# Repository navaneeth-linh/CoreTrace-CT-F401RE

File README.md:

# CT-F401RE Evaluation Board
**Team:** CoreTrace  
**Designer:** S Navaneeth Krishna  
**Institution:** Muthoot Institute of Technology and Science (MITS), Kerala  
**Competition:** Mixed Traces PCB Design Competition — MEC 2026  

---

## Overview
CT-F401RE is a compact STM32F401RET6 evaluation and development board 
designed for the Mixed Traces PCB Design Competition organized by 
Mixed Signals, the Electronics Association of MEC. The board is 
inspired by the STM32 NUCLEO-F401RE reference design and provides 
essential facilities for programming, debugging, and general-purpose 
embedded development.

---

## Features
- STM32F401RET6 LQFP-64 microcontroller
- USB Micro-B interface for power and communication
- SWD debug and programming header (6-pin)
- UART communication header (4-pin)
- SPI communication header (6-pin)
- I2C communication header (4-pin)
- 18 GPIO pins exposed via CN1 and CN2 headers
- 8MHz HSE crystal oscillator
- AMS1117-3.3 LDO voltage regulator (5V → 3.3V)
- 4 LED indicators (PWR / USR / TX / RX)
- Reset tactile button
- User tactile button
- BOOT0 SPDT slide switch
- 100 × 100mm 2-layer PCB
- Designed in KiCad 10.0.5

---

## Design Decisions

### Power Supply
- AMS1117-3.3 LDO chosen for simplicity, availability and low cost
- USB Micro-B as power input via VBUS (5V)
- Bulk capacitors (22µF) on both input and output of regulator
- 100nF ceramic decoupling caps on all MCU VDD pins
- Ferrite bead (120R) on VDDA/VREF+ supply for analog noise filtering
- VCAP1 = 2.2µF for STM32F401RE internal voltage regulator stability

### USB
- 22Ω series resistors on D+ and D− for signal integrity
- Internal 1.5kΩ pullup on D+ for USB Full Speed detection
- USB Micro-B connector on board edge for easy access

### Clock
- 8MHz HSE crystal with 20pF load capacitors
- Crystal placed close to PH0/PH1 pins for short traces

### BOOT0
- SPDT slide switch for easy BOOT0 selection
- FLASH position → normal boot from flash
- BOOT position → bootloader mode
- 10kΩ pulldown resistor as default LOW state

### GPIO
- CN1 exposes: 3.3V, PA0, PA1, PA8, PA9, PA10, PA15, PB1, PB2, GND
- CN2 exposes: 3.3V, PB3, PB4, PB5, PB6, PB7, PB10, PB12, PB13, GND
- All unused PC pins assigned no-connect flags

### PCB
- SMD components throughout for compact layout
- 0402 package for resistors and small capacitors
- 0805 package for LEDs and bulk capacitors
- GND copper pour on both layers
- Track widths: 0.2mm signal, 0.3mm MCU power, 0.5mm 3.3V, 0.8mm VBUS

---

## Design Status

| Task | Status |
|---|---|
| Schematic | ✅ Complete |
| ERC | ✅ Clean (0 errors, 0 warnings) |
| PCB Layout | ✅ Complete |
| Routing | ✅ Complete |
| DRC | ✅ Clean (0 errors, 1 warning) |
| Silkscreen | ✅ Complete |
| BOM | ✅ Complete |
| Documentation | ✅ Complete |

---

## Known Issues and Warnings

### DRC Warning — Footprint Mismatch
**Warning:**    

**Component:** SW1 — BOOT0 SPDT Switch

**Reason:** The SPDT switch footprint was 
modified to fix a silkscreen overlap with 
the board edge cut. The silkscreen of the 
original footprint extended beyond the PCB 
boundary causing a DRC violation. The 
footprint silkscreen was moved inward 
resulting in a minor library mismatch warning.

**Impact:** None — footprint is electrically 
correct and physically accurate. This is a 
cosmetic library mismatch only.

**DRC Summary:**
| Type | Count |
|---|---|
| Errors | 0 ✅ |
| Warnings | 1 ⚠️ |
| Unconnected nets | 0 ✅ |

---

## Screenshots

### Block Diagram 

### Schematic

### PCB Layout

### PCB 3D View

### PCB 3D View

### ERC Results

### DRC Results

---

## Bill of Materials (BOM) with Estimated Cost

| Ref | Component | Value | Package | Qty | Unit Price (₹) | Total (₹) |
|---|---|---|---|---|---|---|
| U1 | STM32F401RET6 | MCU | LQFP-64 | 1 | ₹450 | ₹450 |
| U2 | AMS1117-3.3 | LDO Regulator | SOT-223 | 1 | ₹15 | ₹15 |
| Y1 | Crystal | 8MHz | SMD 3225 | 1 | ₹25 | ₹25 |
| C1, C2 | Capacitor | 22µF | 0805 | 2 | ₹5 | ₹10 |
| C13 | Capacitor | 2.2µF | 0805 | 1 | ₹4 | ₹4 |
| C14, C15 | Capacitor | 1µF | 0805 | 2 | ₹3 | ₹6 |
| C6,C7,C8,C9,C10,C11 | Capacitor | 100nF | 0402 | 6 | ₹2 | ₹12 |
| C3, C12 | Capacitor | 10nF | 0402 | 2 | ₹2 | ₹4 |
| C4, C5 | Capacitor | 20pF | 0402 | 2 | ₹2 | ₹4 |
| R2, R6 | Resistor | 10kΩ | 0402 | 2 | ₹1 | ₹2 |
| R3, R4 | Resistor | 4.7kΩ | 0402 | 2 | ₹1 | ₹2 |
| R1 | Resistor | 1kΩ | 0402 | 1 | ₹1 | ₹1 |
| R5, R7, R8 | Resistor | 330Ω | 0402 | 3 | ₹1 | ₹3 |
| R9, R10 | Resistor | 22Ω | 0402 | 2 | ₹1 | ₹2 |
| R_USB | Resistor | 1.5kΩ | 0402 | 1 | ₹1 | ₹1 |
| FB1 | Ferrite Bead | 120R | 0805 | 1 | ₹8 | ₹8 |
| D1 | LED | Red | 0805 | 1 | ₹5 | ₹5 |
| D2 | LED | Green | 0805 | 1 | ₹5 | ₹5 |
| D3 | LED | Blue | 0805 | 1 | ₹5 | ₹5 |
| D4 | LED | Yellow | 0805 | 1 | ₹5 | ₹5 |
| SW2 | Tactile Switch | Reset | SMD 6×6mm | 1 | ₹8 | ₹8 |
| SW3 | Tactile Switch | User | SMD 6×6mm | 1 | ₹8 | ₹8 |
| SW1 | SPDT Switch | BOOT0 | SMD | 1 | ₹12 | ₹12 |
| J1 | USB Micro-B | Connector | SMD | 1 | ₹20 | ₹20 |
| CN1, CN2 | Pin Header | 2.54mm 1×10 | THT | 2 | ₹8 | ₹16 |
| J5 | Pin Header | 2.54mm 1×06 | THT | 1 | ₹5 | ₹5 |
| J2, J3 | Pin Header | 2.54mm 1×04 | THT | 2 | ₹4 | ₹8 |
| J4 | Pin Header | 2.54mm 1×06 | THT | 1 | ₹5 | ₹5 |
| — | PCB Manufacturing | 2-layer 100×100mm | — | 1 | ₹150 | ₹150 |
| **Total** | | | | | | **₹811** |

> **Note:** Prices are approximate Indian market rates
> sourced from Robu.in, Evelta, and ElectronicsComp.
> Actual prices may vary by supplier and quantity.
> PCB cost based on single unit prototype pricing.

## Tools Used
- KiCad 10.0.5
- STM32F401RET6 Datasheet
- NUCLEO-F401RE Reference Schematic (MB1136)
- STM32F401RE Reference Manual

---

## Competition Details
**Competition:** Mixed Traces PCB Design Competition  
**Organizer:** Mixed Signals — Electronics Association of MEC  
**Reference:** STM32 NUCLEO-F401RE (MB1136)  
**Submission Date:** September 2026  

---

*© 2026 CoreTrace — S Navaneeth Krishna — MITS Kerala*

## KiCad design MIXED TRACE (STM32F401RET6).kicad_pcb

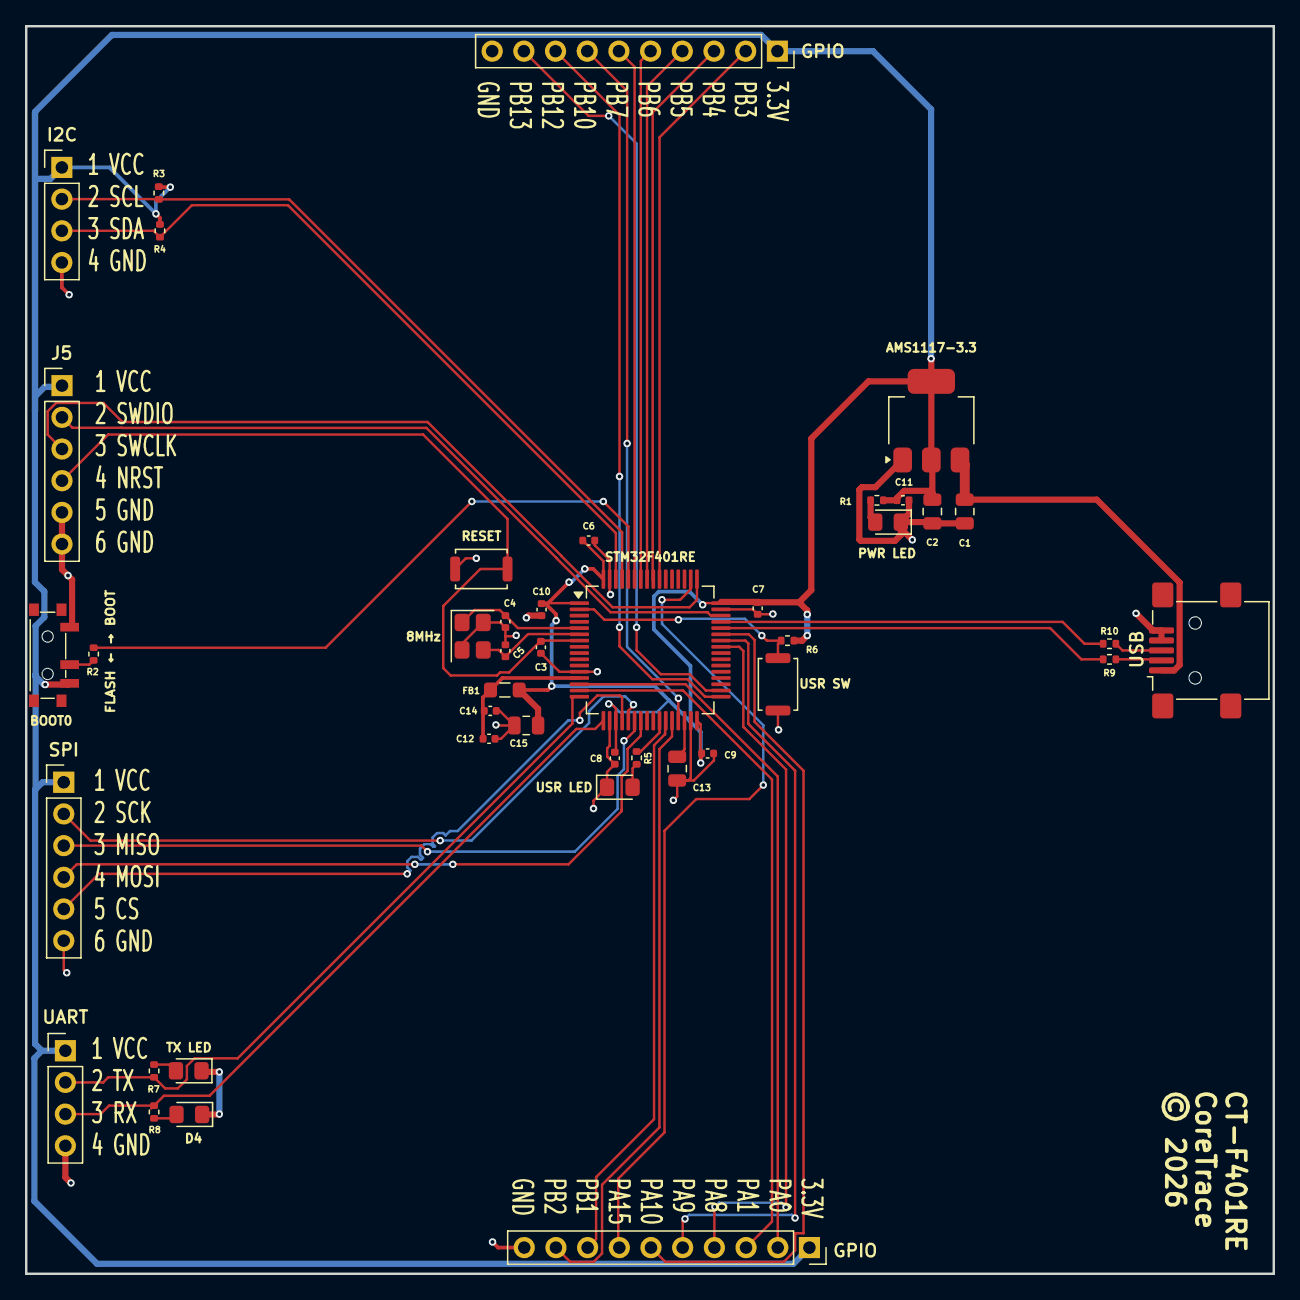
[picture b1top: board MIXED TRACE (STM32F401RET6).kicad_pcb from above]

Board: 2 copper layers, 100.0 x 100.0 mm, 43 parts (0 on the bottom side), 46 nets.

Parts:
8MHz: 8MHz; Crystal_SMD_3225-4Pin_3.2x2.5mm
AMS1117-3.3: AMS1117-3.3; SOT-223-3_TabPin2
BOOT0: BOOT_SW; SW_SPDT_PCM12
C1, C2: 22uF; C_0805_2012Metric
C3, C6, C7, C8, C9, C10, C11: 100nF; C_0402_1005Metric
C4, C5: 20pF; C_0402_1005Metric
C12, C14: 10nF; C_0402_1005Metric
C13: 2.2uF; C_0805_2012Metric
C15: 1uF; C_0805_2012Metric
D4: YELLOW; LED_0805_2012Metric_Pad1.15x1.40mm_HandSolder
FB1: 120R; L_0805_2012Metric_Pad1.05x1.20mm_HandSolder
GPIO: GPIO; PinSocket_1x10_P2.54mm_Vertical
GPIO#2: GPIO; PinSocket_1x10_P2.54mm_Vertical
I2C: I2C; PinHeader_1x04_P2.54mm_Vertical
J5: SWD; PinHeader_1x06_P2.54mm_Vertical
PWR LED: RED; LED_0805_2012Metric_Pad1.15x1.40mm_HandSolder
R1: 1K; R_0402_1005Metric
R2, R6: 10K; R_0402_1005Metric
R3, R4: 4K7; R_0402_1005Metric
R5, R7, R8: 330R; R_0402_1005Metric
R9, R10: 22R; R_0402_1005Metric
RESET: RESET_SW; SW_Push_SPST_NO_Alps_SKRK
SPI: SPI; PinHeader_1x06_P2.54mm_Vertical
STM32F401RE: STM32F401RE; LQFP-64_10x10mm_P0.5mm
TX LED: BLUE; LED_0805_2012Metric_Pad1.15x1.40mm_HandSolder
UART: UART; PinHeader_1x04_P2.54mm_Vertical
USB: USB_B_Micro; USB_Mini-B_Lumberg_2486_01_Horizontal
USR LED: USR_LED_GREEN; LED_0805_2012Metric_Pad1.15x1.40mm_HandSolder
USR SW: USER_SW; SW_Push_SPST_NO_Alps_SKRK

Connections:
+3.3V: AMS1117-3.3.2 (VO), BOOT0.3 (C), C2.1, C6.1, C7.1, C8.1, C9.1, C10.1, C11.1, C15.1, FB1.2, GPIO.1, GPIO#2.1, I2C.1, J5.1, R1.1, R3.1, R4.1, R6.2, SPI.1, STM32F401RE.1 (VBAT), STM32F401RE.19 (VDD), STM32F401RE.32 (VDD), STM32F401RE.48 (VDD), STM32F401RE.64 (VDD), UART.1
+3.3VA: C12.1, C14.1, FB1.1, STM32F401RE.13 (VREF+)
/A0: GPIO#2.2, STM32F401RE.14 (PA0)
/A1: GPIO#2.3, STM32F401RE.15 (PA1)
/A8: GPIO#2.4, STM32F401RE.41 (PA8)
/A9: GPIO#2.5, STM32F401RE.42 (PA9)
/A10: GPIO#2.6, STM32F401RE.43 (PA10)
/A15: GPIO#2.7, STM32F401RE.50 (PA15)
/BOOT_0: R2.2, STM32F401RE.60 (BOOT0)
/CS: SPI.5, STM32F401RE.20 (PA4)
/D+ (USB): R10.1, USB.3 (D+)
/D- (USB): R9.1, USB.2 (D-)
/HSE_IN: 8MHz.1, C4.1, STM32F401RE.5 (PH0)
/HSE_OUT: 8MHz.3, C5.1, STM32F401RE.6 (PH1)
/I2C_SCL: I2C.2, R3.2, STM32F401RE.61 (PB8)
/I2C_SDA: I2C.3, R4.2, STM32F401RE.62 (PB9)
/MISO: SPI.3, STM32F401RE.22 (PA6)
/MOSI: SPI.4, STM32F401RE.23 (PA7)
/NRST: C3.1, J5.4, RESET.2, STM32F401RE.7 (NRST)
/PB1: GPIO#2.8, STM32F401RE.27 (PB1)
/PB2: GPIO#2.9, STM32F401RE.28 (PB2)
/PB3: GPIO.2, STM32F401RE.55 (PB3)
/PB4: GPIO.3, STM32F401RE.56 (PB4)
/PB5: GPIO.4, STM32F401RE.57 (PB5)
/PB6: GPIO.5, STM32F401RE.58 (PB6)
/PB7: GPIO.6, STM32F401RE.59 (PB7)
/PB10: GPIO.7, STM32F401RE.29 (PB10)
/PB12: GPIO.8, STM32F401RE.33 (PB12)
/PB13: GPIO.9, STM32F401RE.34 (PB13)
/PWR_LED_A: PWR LED.2 (A), R1.2
/Rx_LED: D4.2 (A), R8.1
/SCK: SPI.2, STM32F401RE.21 (PA5)
/SWCLK: J5.3, STM32F401RE.49 (PA14)
/SWDIO: J5.2, STM32F401RE.46 (PA13)
/Tx_LED: R7.1, TX LED.2 (A)
/UART_RX: R8.2, STM32F401RE.17 (PA3), UART.3
/UART_TX: R7.2, STM32F401RE.16 (PA2), UART.2
/USR_LED: R5.2, STM32F401RE.26 (PB0)
/USR_SW: R6.1, STM32F401RE.2 (PC13), USR SW.2
/VCAP1: C13.2, STM32F401RE.30 (VCAP1)
GND: 8MHz.2 (G), 8MHz.4 (G), AMS1117-3.3.1 (GND), BOOT0.1 (A), C1.2, C2.2, C3.2, C4.2, C5.2, C6.2, C7.2, C8.2, C9.2, C10.2, C11.2, C12.2, C13.1, C14.2, C15.2, D4.1 (K), GPIO.10, GPIO#2.10, I2C.4, J5.5, J5.6, PWR LED.1 (K), RESET.1, SPI.6, STM32F401RE.12 (VSSA), STM32F401RE.18 (VSS), STM32F401RE.31 (VSS), STM32F401RE.47 (VSS), STM32F401RE.63 (VSS), TX LED.1 (K), UART.4, USB.4 (ID), USB.5 (GND), USR LED.1 (K), USR SW.1
unnamed: R5.1, USR LED.2 (A)
unnamed: BOOT0.2 (B), R2.1
unnamed: R9.2, STM32F401RE.44 (PA11)
unnamed: R10.2, STM32F401RE.45 (PA12)
VBUS: AMS1117-3.3.3 (VI), C1.1, USB.1 (VBUS)
